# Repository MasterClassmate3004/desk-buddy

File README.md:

<h2>DESK STUDY BUDDY</h2>

Built for company while long study sessions right on your desk!

It includes 4 screen pages, has an in-built Pomodoro time tracker for increased focus during sessions, battery level indication and it also blinks. The 3D case is nearly a cube and less than 10cm in each dimension. It is small, doesn't use up too much space on your desk so that you can read more books at once!

<h3>Detailed Components List:</h3>

| Component | Quantity | Status | Price (INR) |
|---|---:|---|---:|
| DFRobot Beetle ESP32-C3 RISC-V development board | 1 | Order | 1009 |
| Waveshare 128×128 1.5-inch OLED display module | 1 | Order | 1369 |
| ACEBOTT passive buzzer module | 1 | Order | 239 |
| NOVA 603048 3.7V 900mAh LiPo battery pack | 1 | Already have | — |
| Cherry MX switches | 3 | Already have | — |
| 10 kΩ resistor | 1 | Already have | — |
| 100 kΩ resistors | 2 | Already have | — |
| 100 nF capacitor | 1 | Already have | — |
| 2.54 mm 1×08 OLED header | 1 | Already have | — |
| 2.54 mm 1×03 buzzer header | 1 | Already have | — |
| Desk Buddy custom PCB | 1 | Buy | — |
| 3D-printed enclosure | 1 | Print separately | — |

<h3>Schematics</h3>
<br>
This is the schematics design for the Desk Buddy that defines all the connections across each component.

<h3>PCB</h3>
<br>
This is the PCB design for the Desk Buddy that routes all components and places them as they will be placed in the final PCB.

<br><br>
After you print your PCB and receive all the require components, it is time to solder them to their respective places as indicated in the PCB. Except the components to be soldered on the PCB, you also need to solder the li-po battery's terminals onto your ESP32-C3.
<br>

<h3>PCB 3D view</h3>
This is the expected 3D view of the expected PCB after soldering of all components.

<br><br>
After soldering the PCB, screw the OLED display on to the front of the main case in the specific holes, ensuring the display is visible through the gap. 
After that, place the PCB on the 4 tall legs inside the main case shown and ensure they are fixed there. Place the Li-Po battery down so that it does not interfere with the placement of the Top Case later.

<br>
<h3>Main Case</h3>
This is the main case of the Desk Buddy

<br><br>
After placing the PCB and OLED display in the require positions, use the Top Cover to close the desk buddy ensuring the key caps easily come out of the given gaps. Stick the Top Cover to the main case firmly.

<h3>Top Cover</h3>
This is the Top Cover for the Desk Buddy.

<br><br>
The mechanical build for the Desk Buddy is ready. Now only the firmware awaits.

<h3>Final Assembly</h3>
This is the expected final look of the desk buddy!

<br><br>
For firmware, connect your ESP32-C3 with your computer with a cable. Open your Arduino IDE and select the required board and port. Lastly upload the firmware code (that can be downloaded from this repo) through the Arduino IDE and we are done. 

Our Desk Buddy would also work without connecting to the computer all the time as we have a separate battery to power it. The firmware also shows the battery level on our OLED display so you will need to keep charging the Desk Buddy as and when required. 

Thank you! Let's all keep studying with our desk study buddy!

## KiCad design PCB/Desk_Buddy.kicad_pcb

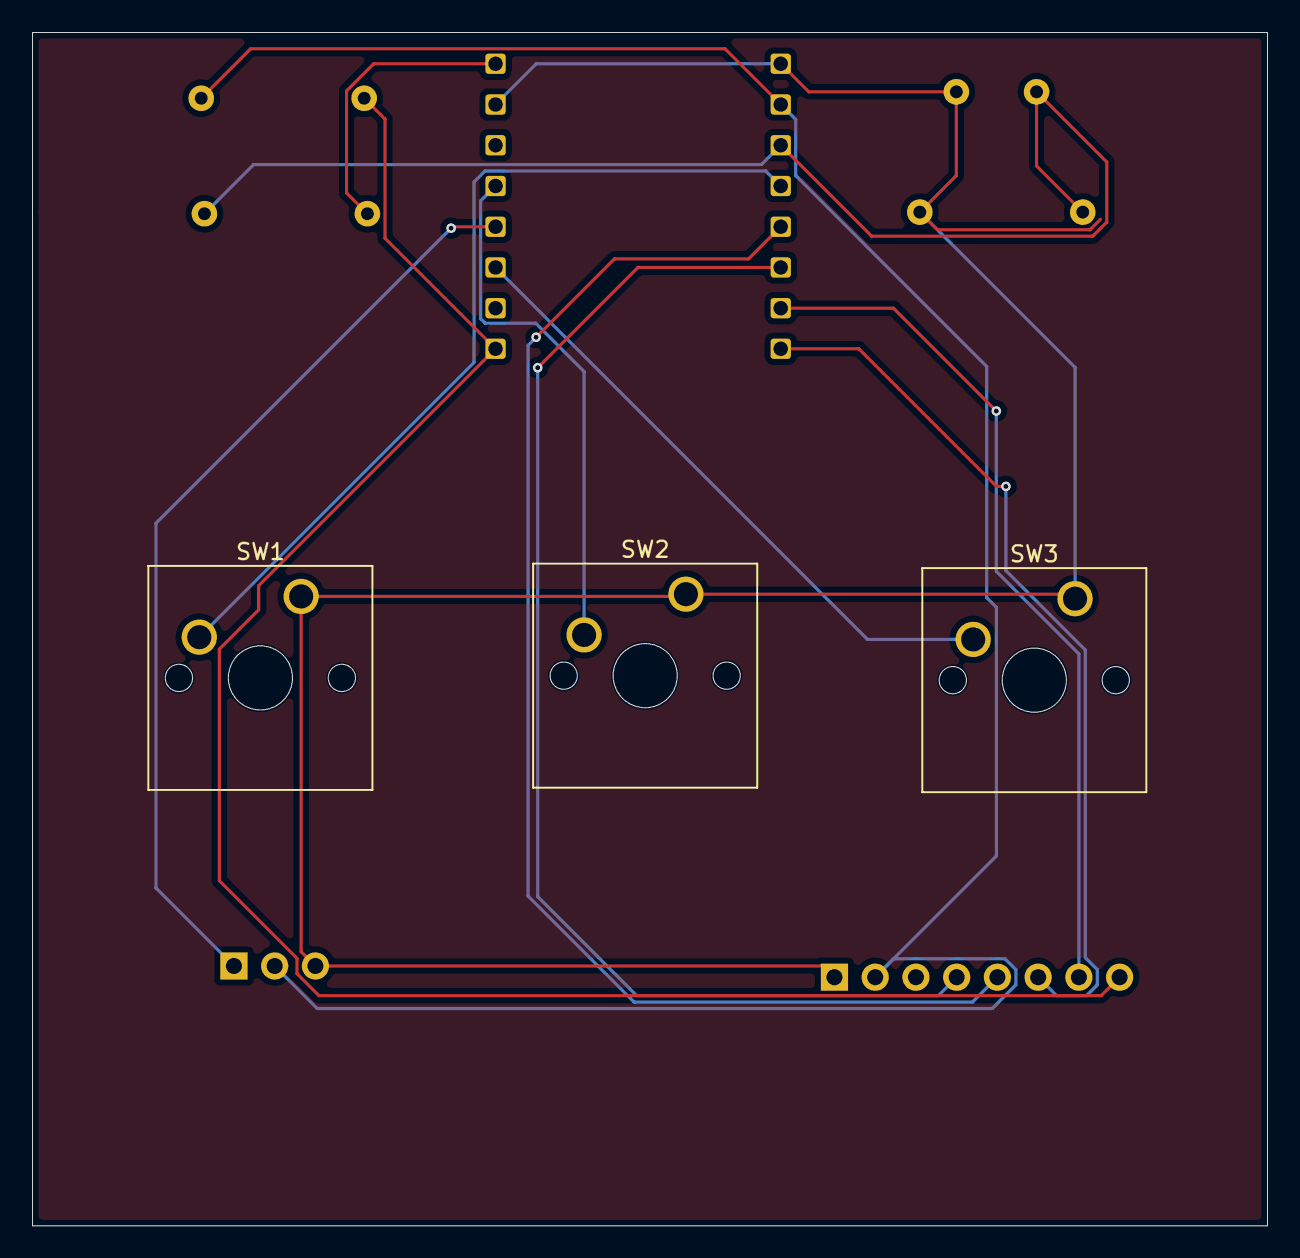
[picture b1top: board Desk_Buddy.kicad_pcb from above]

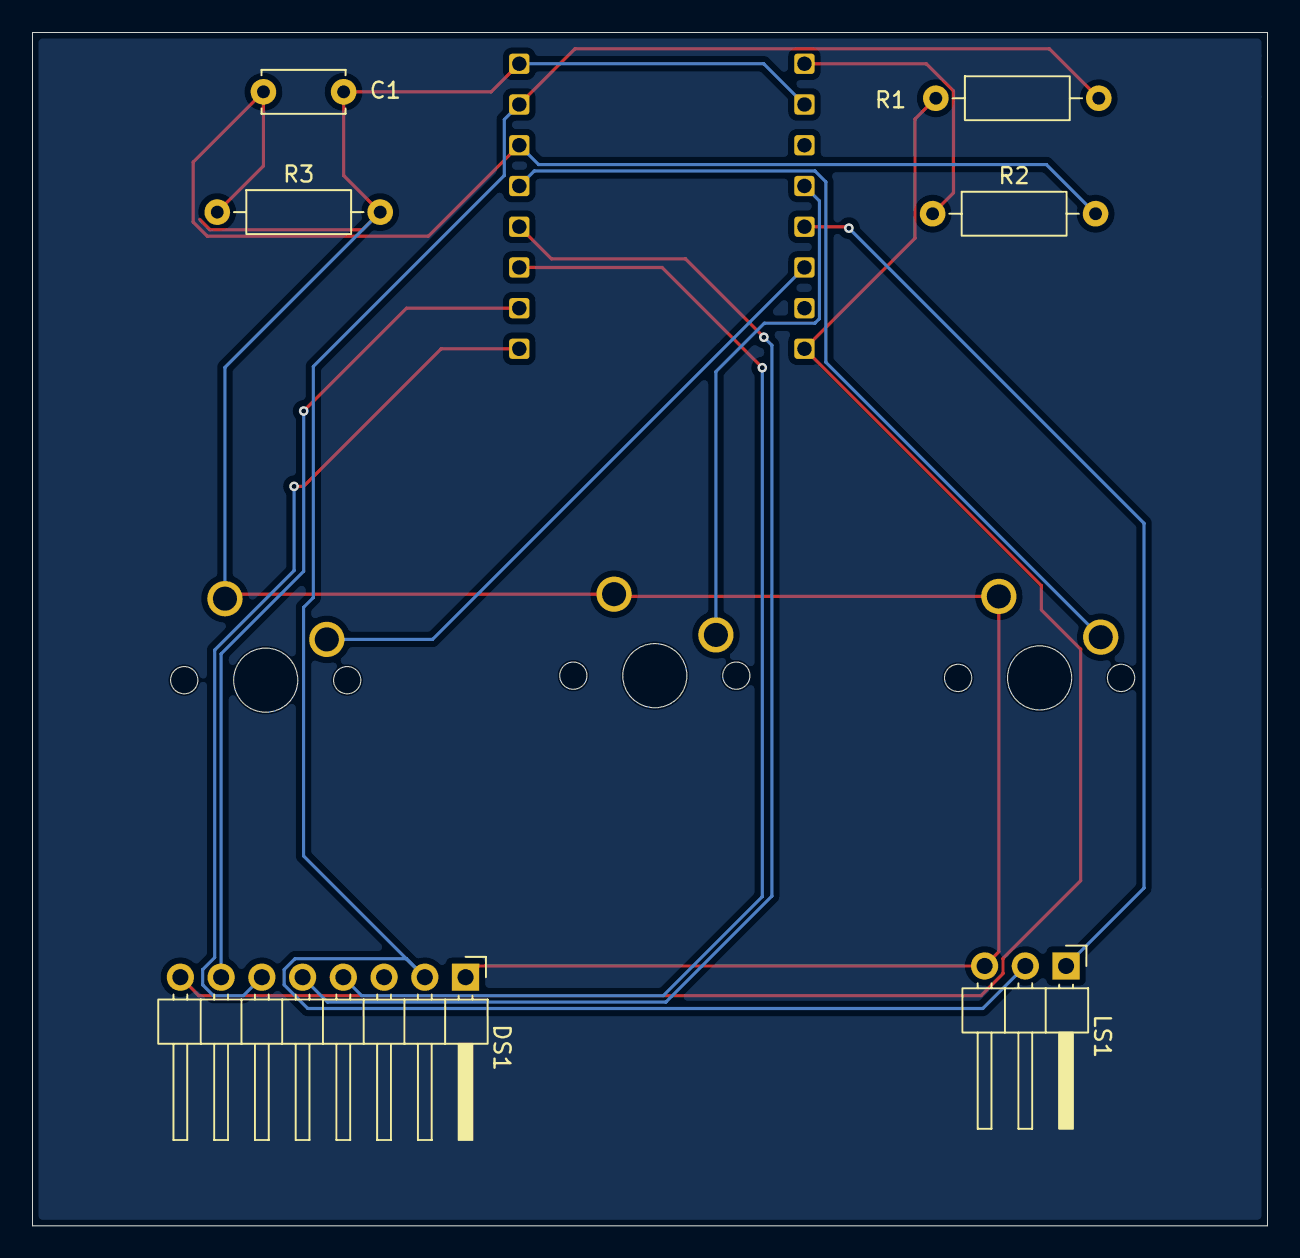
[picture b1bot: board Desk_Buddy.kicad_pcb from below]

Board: 2 copper layers, 77.0 x 74.4 mm, 10 parts (7 on the bottom side), 13 nets.

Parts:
C1: 100nF; C_Disc_D5.0mm_W2.5mm_P5.00mm
DS1: PinHeader_1x08_P2.54mm_Horizontal
LS1: PinHeader_1x03_P2.54mm_Horizontal
R1: 10K; R_Axial_DIN0207_L6.3mm_D2.5mm_P10.16mm_Horizontal
R2, R3: 100K; R_Axial_DIN0207_L6.3mm_D2.5mm_P10.16mm_Horizontal
SW1, SW2, SW3: SW_Push; SW_Cherry_MX_1.00u_PCB
U1: Untitled

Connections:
/3V3: DS1.2 (VCC), LS1.2 (V), R1.2, U1.2 (3V3)
/CLK: DS1.5 (CLK), U1.5 (GPIO4)
/CS: DS1.6 (CS), U1.8 (GPIO7)
/DC: DS1.7 (DC), U1.7 (GPIO5)
/DIN: DS1.4 (DIN), U1.6 (GPIO6)
/RST: DS1.8 (RST), R1.1, U1.16 (GPIO2)
/S1: SW1.2, U1.4 (GPIO1)
/S2: SW2.2, U1.12 (GPIO20_RX)
/S3: SW3.2, U1.14 (GPIO8)
/SIG: LS1.1 (S), U1.13 (GPIO21_TX)
/V_BATS: C1.1, R2.2, R3.1, U1.3 (GPIO0)
GND: C1.2, DS1.1 (GND), LS1.3 (G), R3.2, SW1.1, SW2.1, SW3.1, U1.1 (GND), U1.10 (GND)
unnamed: R2.1, U1.9 (BAT)
